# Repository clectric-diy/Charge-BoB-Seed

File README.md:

# First Render
Here is the first render of our Daisy Seed Breakout Board :

The goal is to create a breakout board that contains the reference information that you need to work with the Daisy Seed.

It's hard to tell without a 3D perspective, but those are female headers for the seed to plug into with both male and female headers available to use as well as screw terminal blocks.

Constructive [feedback](https://github.com/orgs/clectric-diy/discussions/39) is welcome!

# License
This project is open hardware under the [CERN-OHL-S](https://gitlab.com/ohwr/project/cernohl/-/wikis/uploads/b236492596cfc91c12def7d50bbf7da0/cern_ohl_s_v2.pdf) license.

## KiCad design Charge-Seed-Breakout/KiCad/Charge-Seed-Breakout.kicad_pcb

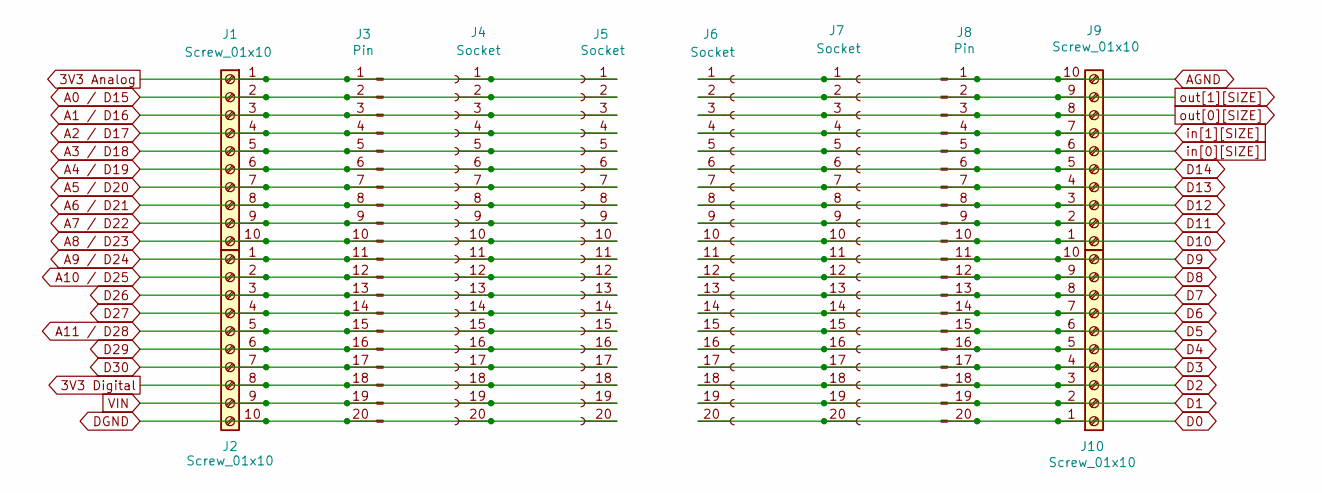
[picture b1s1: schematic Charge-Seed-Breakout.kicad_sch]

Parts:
J1, J2, J9, J10: Screw_01x10; TerminalBlock_Phoenix_MPT-0,5-10-2.54_1x10_P2.54mm_Horizont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
J3, J8: Pin; PinHeader_1x20_P2.54mm_Vertical
J4, J5, J6, J7: Socket; PinSocket_1x20_P2.54mm_Vertical

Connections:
3V3 Analog: J1.1, J3.1, J4.1, J5.1
3V3 Digital: J2.8, J3.18, J4.18, J5.18
A0 / D15: J1.2, J3.2, J4.2, J5.2
A1 / D16: J1.3, J3.3, J4.3, J5.3
A2 / D17: J1.4, J3.4, J4.4, J5.4
A3 / D18: J1.5, J3.5, J4.5, J5.5
A4 / D19: J1.6, J3.6, J4.6, J5.6
A5 / D20: J1.7, J3.7, J4.7, J5.7
A6 / D21: J1.8, J3.8, J4.8, J5.8
A7 / D22: J1.9, J3.9, J4.9, J5.9
A8 / D23: J1.10, J3.10, J4.10, J5.10
A9 / D24: J2.1, J3.11, J4.11, J5.11
A10 / D25: J2.2, J3.12, J4.12, J5.12
A11 / D28: J2.5, J3.15, J4.15, J5.15
AGND: J6.1, J7.1, J8.1, J9.10
D0: J6.20, J7.20, J8.20, J10.1
D1: J6.19, J7.19, J8.19, J10.2
D2: J6.18, J7.18, J8.18, J10.3
D3: J6.17, J7.17, J8.17, J10.4
D4: J6.16, J7.16, J8.16, J10.5
D5: J6.15, J7.15, J8.15, J10.6
D6: J6.14, J7.14, J8.14, J10.7
D7: J6.13, J7.13, J8.13, J10.8
D8: J6.12, J7.12, J8.12, J10.9
D9: J6.11, J7.11, J8.11, J10.10
D10: J6.10, J7.10, J8.10, J9.1
D11: J6.9, J7.9, J8.9, J9.2
D12: J6.8, J7.8, J8.8, J9.3
D13: J6.7, J7.7, J8.7, J9.4
D14: J6.6, J7.6, J8.6, J9.5
D26: J2.3, J3.13, J4.13, J5.13
D27: J2.4, J3.14, J4.14, J5.14
D29: J2.6, J3.16, J4.16, J5.16
D30: J2.7, J3.17, J4.17, J5.17
DGND: J2.10, J3.20, J4.20, J5.20
VIN: J2.9, J3.19, J4.19, J5.19
in[0][SIZE]: J6.5, J7.5, J8.5, J9.6
in[1][SIZE]: J6.4, J7.4, J8.4, J9.7
out[0][SIZE]: J6.3, J7.3, J8.3, J9.8
out[1][SIZE]: J6.2, J7.2, J8.2, J9.9

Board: 2 copper layers, 10 parts (0 on the bottom side), 40 nets, no tracks yet.

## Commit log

2025-08-24 Create LICENSE
2025-08-24 Adding Architect Theme
2025-08-24 Adding First Sketch
2025-08-24 Fixing filename and link to image
2025-08-24 testing header formatting
2025-08-24 Standard FUNDING & gitignore
2025-08-24 Bump for Pages
2025-09-03 Schematic complete.
2025-09-03 Initial commit of PCB Layout (see remaining tasks)
2025-09-03 Ignoring Gerbers. Trust but verify.
2025-09-04 Added Reference Image in KiCad to be used as Silkscreen on PCB
2025-09-05 Ignoring KiCad Lock files
2025-09-08 Removing sketch. Adding render.
2025-09-08 Adding 1st render.
2025-09-08 1st Render Updates
2025-09-08 Added goal and discussion link.
